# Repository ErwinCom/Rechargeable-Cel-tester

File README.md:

# Rechargeable-Cell-tester
Tester for rechargeable cells (li-ion, li-po, ni-mh, ni-cad)

This tester is derived of the work of: vwlowen

http://vwlowen.co.uk/arduino/battery-tester/batery-tester.htm

Adapted for personal use.

1. Changed PCB layout:
2. no power supply (power is supplied through usb connector)
3. No ftd232
4. changed arduino sketch

Files:

1. PCB, eagle format
2. Schematic, pdf and eagle format
3. casing design, laser cut 3mm plywood
4.

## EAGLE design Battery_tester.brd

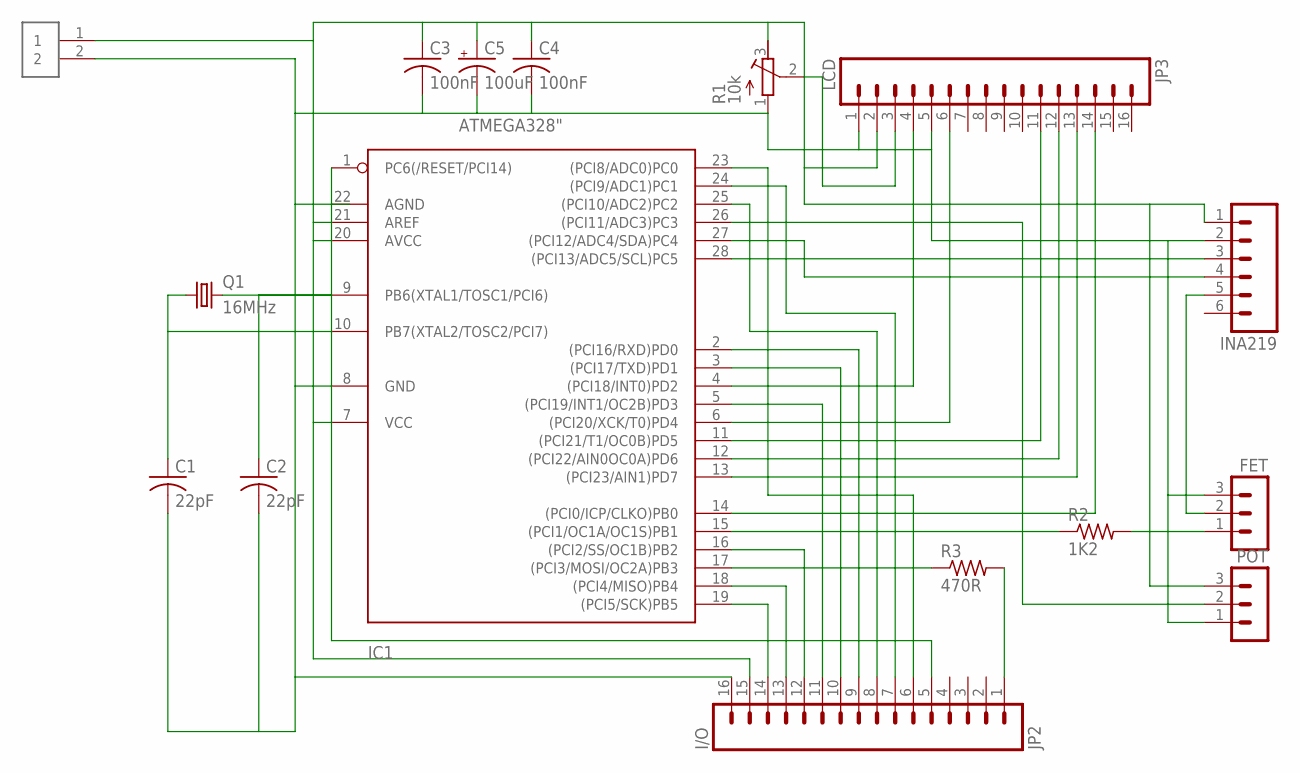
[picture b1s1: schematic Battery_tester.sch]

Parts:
C1, C2: 22pF; UNPOLARIZED_CAP
C3, C4: 100nF; UNPOLARIZED_CAP
C5: 100uF; ELECTROLYTIC_CAP
FET: MA03-1
I/O: JP2; 1X16_HEADER
IC1: ATMEGA328"; ATMEGA328
INA219: 1X06_HEADER"; 1X06_HEADER
JP3: LCD; 1X16_HEADER
POT: MA03-1
Q1: 16MHz; HC18U-V
R1: 10k; RTRIM3339P
R2: 1K2; RESISTOR
R3: 470R; RESISTOR
USB: 5V; 1X02_HEADER

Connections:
unnamed: JP3.3, R1.2 (S)
unnamed: C1.2, C2.2, C3.2, C4.2, C5.-, FET.3, I/O.16, IC1.8 (GND), INA219.2, JP3.1, JP3.5, POT.1, R1.1 (E), USB.2
unnamed: C1.1, IC1.10 (PB7(XTAL2/TOSC2/PCI7)), Q1.1
unnamed: C2.1, IC1.9 (PB6(XTAL1/TOSC1/PCI6)), Q1.2
unnamed: C3.1, C4.1, C5.+, I/O.15, IC1.7 (VCC), IC1.20 (AVCC), IC1.21 (AREF), INA219.1, JP3.2, POT.3, R1.3 (A), USB.1
unnamed: IC1.4 ((PCI18/INT0)PD2), JP3.4
unnamed: IC1.6 ((PCI20/XCK/T0)PD4), JP3.6
unnamed: IC1.11 ((PCI21/T1/OC0B)PD5), JP3.11
unnamed: IC1.12 ((PCI22/AIN0OC0A)PD6), JP3.12
unnamed: IC1.13 ((PCI23/AIN1)PD7), JP3.13
unnamed: IC1.14 ((PCI0/ICP/CLKO)PB0), JP3.14
unnamed: IC1.28 ((PCI13/ADC5/SCL)PC5), INA219.3
unnamed: IC1.27 ((PCI12/ADC4/SDA)PC4), INA219.4
unnamed: IC1.15 ((PCI1/OC1A/OC1S)PB1), R2.1
unnamed: FET.1, R2.2
unnamed: FET.2, INA219.5
unnamed: IC1.26 ((PCI11/ADC3)PC3), POT.2
unnamed: IC1.17 ((PCI3/MOSI/OC2A)PB3), R3.1
unnamed: I/O.1, R3.2
unnamed: I/O.14, IC1.19 ((PCI5/SCK)PB5)
unnamed: I/O.13, IC1.18 ((PCI4/MISO)PB4)
unnamed: I/O.12, IC1.16 ((PCI2/SS/OC1B)PB2)
unnamed: I/O.11, IC1.5 ((PCI19/INT1/OC2B)PD3)
unnamed: I/O.10, IC1.3 ((PCI17/TXD)PD1)
unnamed: I/O.9, IC1.2 ((PCI16/RXD)PD0)
unnamed: I/O.8, IC1.25 ((PCI10/ADC2)PC2)
unnamed: I/O.7, IC1.24 ((PCI9/ADC1)PC1)
unnamed: I/O.6, IC1.23 ((PCI8/ADC0)PC0)
unnamed: I/O.5, IC1.1 (PC6(/RESET/PCI14))

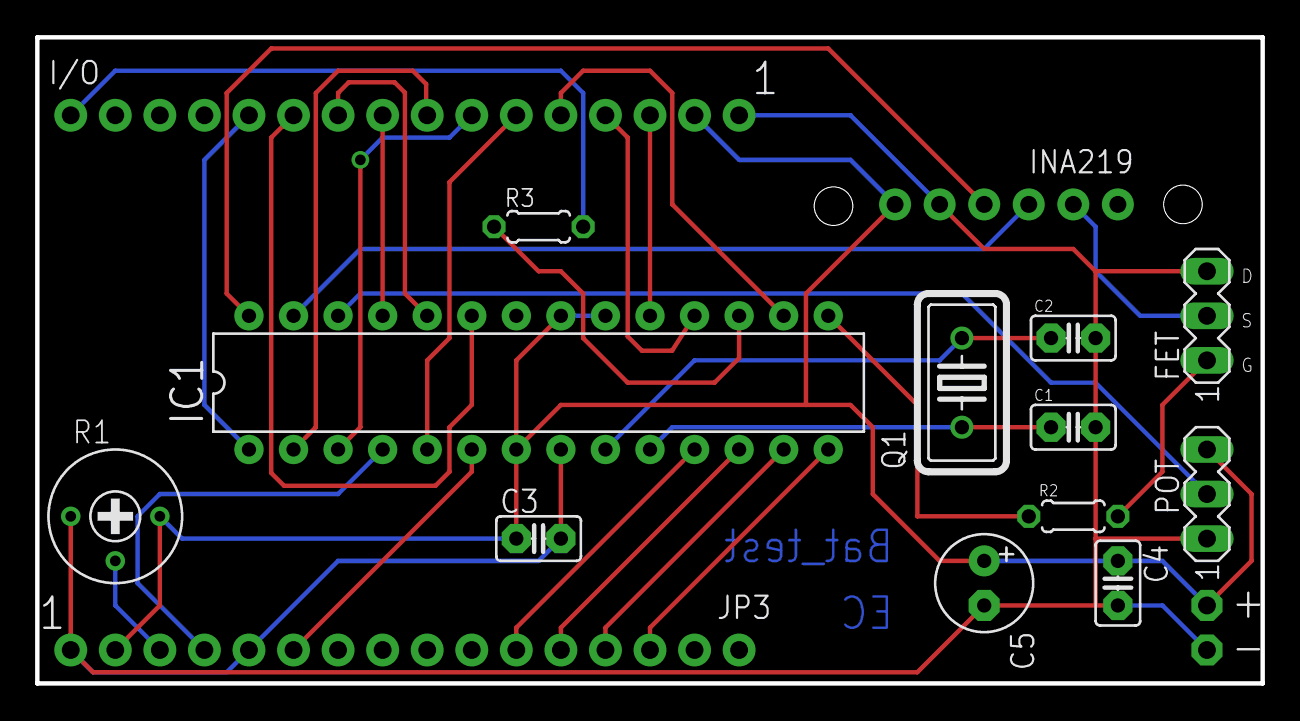
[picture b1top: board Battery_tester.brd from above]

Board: 2 copper layers, 69.8 x 36.8 mm, 16 parts (0 on the bottom side), 29 nets.
